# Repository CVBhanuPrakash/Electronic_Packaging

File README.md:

# PCB Design for FM Transmitter

This project involves the design of both schematic and PCB layout for an FM Transmitter circuit using Eagle Software. The primary goals of this project were to create an efficient and compact PCB design with proper interconnections.

## Project Highlights:

- **Schematic Design:** The project initiates with the schematic design, meticulously planning the components and their connections to ensure the functionality of the FM Transmitter circuit.

- **Compact PCB Layout:** The PCB layout was a key focus, with the aim of reducing the size as much as possible while maintaining proper interconnections. This helps in optimizing the circuit for space-constrained applications.

- **Double-Sided PCB:** To further minimize the PCB size and enhance efficiency, double-sided PCBs were utilized for component placement.

- **Gerber Files:** For reference and manufacturing purposes, the project includes a Gerber files folder containing the design files necessary for PCB fabrication.

## Course Project:

This project was completed as part of my Electronic Packaging course. It reflects my proficiency in electronic design, PCB layout, and optimization techniques for electronic circuits.

## Documentation and Resources:

For detailed project information and design files, please refer to the provided [PowerPoint Presentation](https://github.com/CVBhanuPrakash/Electronic_Packaging/blob/main/GROUP-19_EP_PROJECT.pptx) and the Gerber files folder in respository.

## Preview Image:

By designing this FM Transmitter circuit and optimizing its PCB layout, this project demonstrates my skills in electronic design and packaging.

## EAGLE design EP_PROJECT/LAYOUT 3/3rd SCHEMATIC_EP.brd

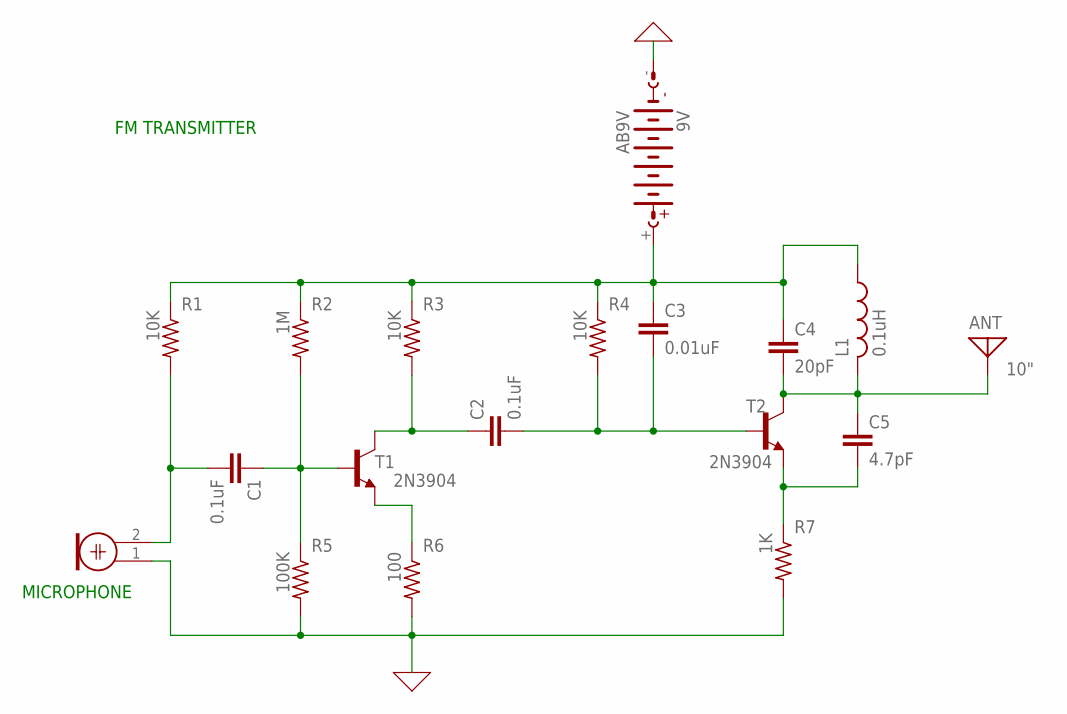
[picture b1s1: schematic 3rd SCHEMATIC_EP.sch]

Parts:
9V: AB9V
ANT: 10"; PAD-01
C1, C2: 0.1uF; C2.5-2
C3: 0.01uF; C2.5-2
C4: 20pF; C2.5-2
C5: 4.7pF; C2.5-2
L1: 0.1uH; 0207/7
MICROPHONE: ELECTRET_MICROPHON-F6050AP; F6050AP
R1, R3, R4: 10K; R0603
R2: 1M; R0603
R5: 100K; R0603
R6: 100; R0603
R7: 1K; R0603
T1, T2: 2N3904; TO92

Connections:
0: 9V.-, MICROPHONE.1, R5.2, R6.2, R7.2
unnamed: C1.1, R2.2, R5.1, T1.2 (B)
unnamed: R6.1, T1.3 (E)
unnamed: C2.1, R3.2, T1.1 (C)
unnamed: 9V.+, C3.1, C4.1, L1.1, R1.1, R2.1, R3.1, R4.1
unnamed: C1.2, MICROPHONE.2, R1.2
unnamed: C5.2, R7.1, T2.3 (E)
unnamed: C2.2, C3.2, R4.2, T2.2 (B)
unnamed: ANT.1, C4.2, C5.1, L1.2, T2.1 (C)

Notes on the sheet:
MICROPHONE
FM TRANSMITTER

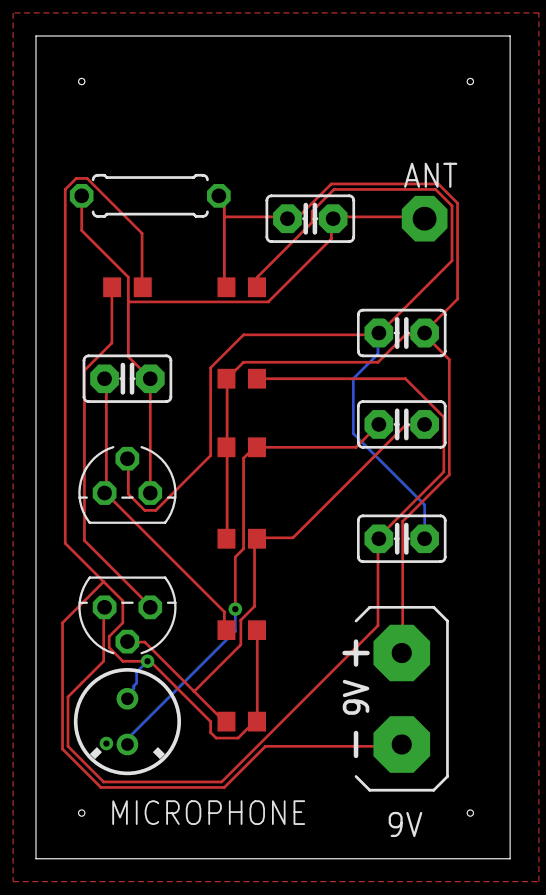
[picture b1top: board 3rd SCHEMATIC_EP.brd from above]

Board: 2 copper layers, 26.3 x 45.7 mm, 18 parts (0 on the bottom side), 9 nets.

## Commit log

2023-02-01 files added
2023-02-16 FINAL
